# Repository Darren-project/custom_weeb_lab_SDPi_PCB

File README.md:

# PCB for Weeb Lab's SDPi

## What does this PCB do
This PCB features a RP2350 that runs Weeb Lab's [DSPi](https://www.audiosciencereview.com/forum/index.php?threads/introducing-dspi-a-powerful-user-friendly-and-open-source-dsp-for-less-than-a-cup-of-coffee.69343/) which takes in USB Audio from the host pc and allows user to create parametric EQs.
<br> I added the correct caps and resistors to the outputs so that it can be connected to a output devices.
<br> Therefore, I also splitted the SPDIF to a decoder that outputs I2S to a dac and 2 opamps to drive a line out or headphones.

## How to use it
Hold the boot button and download the Weeb Lab's DSPi firmware into it.
<br> Launch the companion app and configure the eq.
<br> At last, connect the device to the output of your choice.

BOM: [Link to CSV](https://github.com/Darren-project/custom_weeb_lab_SDPi_PCB/blob/main/production/bom.csv)

PCB Design <br>

Schematics

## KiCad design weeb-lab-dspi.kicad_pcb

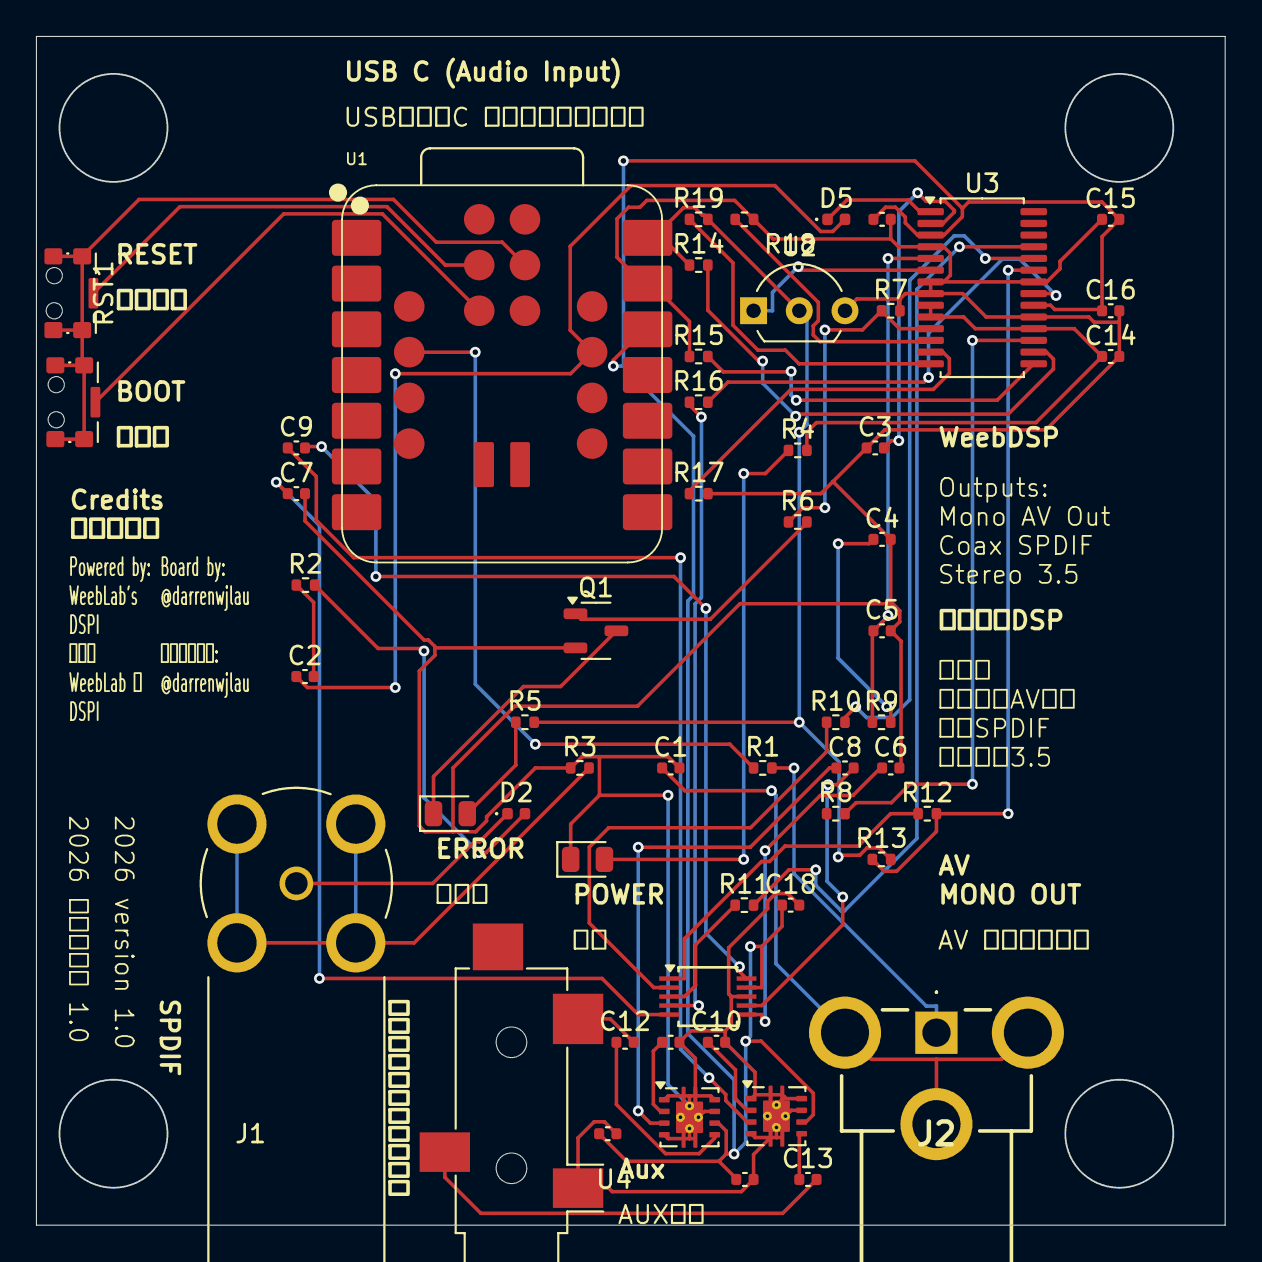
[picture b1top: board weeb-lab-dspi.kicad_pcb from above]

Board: 2 copper layers, 66.0 x 66.0 mm, 55 parts (0 on the bottom side), 50 nets.

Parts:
BOOT1: BOOT; SW_SPST_CK_KMS2xxGP
C1: 47nf; C_0402_1005Metric
C2, C14, C15, C16, C18, C19, C20: 100nf; C_0402_1005Metric
C3: 10nf; C_0402_1005Metric
C4: 22nf; C_0402_1005Metric
C5, C17: 1nf; C_0402_1005Metric
C6, C7, C8, C9, C12, C13: 10uf; C_0402_1005Metric
C10, C11: 0.1uf; C_0402_1005Metric
D2, D5: BACKFEED_PREVENT; D_0402_1005Metric
D3: POWER; LED_0805_2012Metric
D4: ERROR; LED_0805_2012Metric
J1: SPDIF; TE_2466268-1
J2: MONO RCA; 936
J4: AudioJack3_Ground; Jack_3.5mm_CUI_SJ-3524-SMT_Horizontal
LEFT1: TPA6203A1DRB; Texas_DRB0008A
Q1: BC846; SOT-23-3
R1: 3.3k; R_0402_1005Metric
R2: 330; R_0402_1005Metric
R3: 100; R_0402_1005Metric
R4, R5: 1k2; R_0402_1005Metric
R6, R7, R8, R13, R14, R15, R17, R18, R19: 47k; R_0402_1005Metric
R9: 3k; R_0402_1005Metric
R10, R11, R12, R16: 33R; R_0402_1005Metric
RIGHT1: TPA6203A1DRB; Texas_DRB0008A
RST1: RST; SW_SPST_CK_KMS2xxGP
U1: XIAO-RP2350-SMD
U2: MCP130-xxxDxTO; TO-92L_Inline_Wide
U3: CS8416-xNZ; TSSOP-28_4.4x9.7mm_P0.65mm
U4: CS434x-xZZ; TSSOP-10_3x3mm_P0.5mm

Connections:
GND: C1.2, C3.1, C4.2, C5.2, C6.2, C7.2, C10.2, C11.2, C14.2, C15.1, C16.2, C17.2, C18.2, C19.2, C20.2, D3.1 (K), J4.S, LEFT1.1 (~SHUTDOWN), LEFT1.4 (IN-), LEFT1.7 (GND), LEFT1.8 (V_{O-}), LEFT1.9 (GND), Q1.2 (E), R3.1, R7.2, R15.1, R17.2, R18.2, RIGHT1.1 (~SHUTDOWN), RIGHT1.4 (IN-), RIGHT1.7 (GND), RIGHT1.8 (V_{O-}), RIGHT1.9 (GND), U1.13 (GND), U2.3 (VSS), U3.4 (AGND), U3.7 (RXP4/RXSEL1), U3.8 (RXP5/RXSEL0), U3.19 (DGND), U3.22 (OMCK), U4.8 (AGND)
unnamed: BOOT1.SH (B), U1.25 (BOOT)
unnamed: C1.1, J2.MH1, J2.MH2, J2.MH3
unnamed: C2.2, R2.1
unnamed: C4.1, R9.2
unnamed: C12.2, J4.T
unnamed: C13.2, J4.R
unnamed: D2.2 (A), R2.2
unnamed: D2.1 (K), J1.1
unnamed: D3.2 (A), R4.1
unnamed: D4.2 (A), R5.1
unnamed: D4.1 (K), Q1.3 (C)
unnamed: C2.1, D5.2 (A), U1.16 (GPIO20/D12/TX1)
unnamed: D5.1 (K), U3.1 (RXP0)
unnamed: J2.1, R1.2
unnamed: C11.1, LEFT1.2 (BYPASS)
unnamed: C8.1, LEFT1.3 (IN+)
unnamed: C15.2, C16.1, C17.1, C18.1, C19.1, C20.1, LEFT1.6 (V_{DD}), RIGHT1.6 (V_{DD}), U1.12 (3V3), U3.3 (VA), U3.20 (VD), U4.9 (VA)
unnamed: C12.1, LEFT1.5 (V_{O+})
unnamed: Q1.1 (B), R6.2
unnamed: C10.1, RIGHT1.2 (BYPASS)
unnamed: C9.1, RIGHT1.3 (IN+)
unnamed: C13.1, RIGHT1.5 (V_{O+})
unnamed: RST1.SH (B), U1.24 (RST)
unnamed: C14.1, R4.2, R5.2, R13.2, R14.1, R19.2, U1.14 (5V), U2.2 (VDD), U3.9 (RXP6/TXSEL1), U3.10 (RXP7/TXSEL0), U3.18 (VL)
unnamed: BOOT1.1, BOOT1.2, RST1.1, RST1.2, U1.27 (GND_1)
unnamed: R1.1, U1.21 (GPIO10/D17/SPI1_SCK)
unnamed: U2.1 (~RST), U3.6 (~RESET)
unnamed: R6.1, R7.1, U3.11 (AD0/~CS/NV/RERR)
unnamed: R18.1, U3.12 (AD1/CDIN/~AUDIO)
unnamed: R14.2, U3.16 (C/GPO1)
unnamed: C5.1, R9.1, U3.5 (FILT)
unnamed: R11.2, U3.25 (OLRCK)
unnamed: R10.2, U3.24 (OSCLK)
unnamed: R16.2, U3.21 (RMCK)
unnamed: C3.2, U3.2 (RXN)
unnamed: R17.1, U3.13 (SCL/CCLK/96KHZ)
unnamed: R19.1, U3.14 (SDA/CDOUT/RCBL)
unnamed: R12.2, R13.1, U3.23 (SDOUT)
unnamed: R8.2, U3.17 (TX/GPO0)
unnamed: R15.2, U3.15 (U/AD2/GPO2)
unnamed: C8.2, U4.7 (AOUTL)
unnamed: C9.2, U4.10 (AOUTR)
unnamed: C6.1, U4.6 (FILT+)
unnamed: R11.1, U4.3 (LRCK)
unnamed: R16.1, U4.4 (MCLK)
unnamed: R12.1, U4.1 (SDIN)
unnamed: C7.1, U4.5 (VQ)
unnamed: R10.1, U4.2 (~DEM/SCLK)
~: J1.2, J1.3, J1.4, J1.5, R3.2

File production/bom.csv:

Designator,Footprint,Quantity,Value,LCSC Part #
BOOT1,SW_SPST_CK_KMS2xxGP,1,BOOT,
C1,0402,1,47nf,
"C10, C11",0402,2,0.1uf,
"C12, C13, C6, C7, C8, C9",0402,6,10uf,
"C14, C15, C16, C18, C19, C2, C20",0402,7,100nf,
"C17, C5",0402,2,1nf,
C3,0402,1,10nf,
C4,0402,1,22nf,
"D2, D5",0402,2,BACKFEED_PREVENT,
D3,0805,1,POWER,
D4,0805,1,ERROR,
J1,TE_2466268-1,1,SPDIF,
J2,936,1,MONO RCA,
J4,Jack_3.5mm_CUI_SJ-3524-SMT_Horizontal,1,AudioJack3_Ground,
"LEFT1, RIGHT1",Texas_DRB0008A,2,TPA6203A1DRB,
Q1,SOT-23-3,1,BC846,
R1,0402,1,3.3k,
"R10, R11, R12, R16",0402,4,33R,
"R13, R14, R15, R17, R18, R19, R6, R7, R8",0402,9,47k,
R2,0402,1,330,
R3,0402,1,100,
"R4, R5",0402,2,1k2,
R9,0402,1,3k,
RST1,SW_SPST_CK_KMS2xxGP,1,RST,
U1,XIAO-RP2350-SMD,1,XIAO-RP2350-SMD,
U2,TO-92L_Inline_Wide,1,MCP130-xxxDxTO,
U3,TSSOP-28_4.4x9.7mm_P0.65mm,1,CS8416-xNZ,
U4,TSSOP-10_3x3mm_P0.5mm,1,CS434x-xZZ,

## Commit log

2026-02-07 First Day
2026-02-07 Routed PCB and added more parts
2026-02-07 Almost Complete
2026-02-08 Finally
2026-02-08 Add power bypass caps
2026-02-09 Final
2026-02-09 Forgot to close kicad
2026-02-09 add pcb pic
2026-02-11 Adding Labeling
